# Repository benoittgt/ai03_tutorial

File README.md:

# ai03_tutorial

⚠️ This is a prototype that has not been builded for the moment. I am waiting for review ⚠️

Thanks ai03 and Ruiqi Mao for this very good guide (baby steps, shortcuts, many screenshots, electronic tips...).

## Feedbacks for [the original guide](https://kbwiki.ai03.me/books/pcb-design)

### [Part 4](https://kbwiki.ai03.me/books/pcb-design/page/pcb-guide-part-4---the-rest-of-the-schematic)
* Hard to find all schema. I had to import one by one lib from https://github.com/ldoiron17/Kicad_Libraries
* Different menu: "Switch to inch instead of mm on the left pane, and open Setup -> Design Rules." is Board Setup -> Design Rules -> Net classes
* Different menu: "Then click on the first corner of the zone to surround to bring up a menu." the "Copper Zone Properties" is different
### [Part 6](https://kbwiki.ai03.me/books/pcb-design/page/pcb-guide-part-6---fill-zones-decoration-and-production)
* Copper Zone Properties doesn't offer "Boundary mode" anymore
* When I try to simulate the board it's not delimited by the line 
* When I run the DRC the Molex connector have unclosed path so I need to switch
* DRC told be that "Driled holes too close together" for MX-1U

## Result

### PCB from Kicad

### Schema from Kicad

### Gerber file front and back rendered on JLPCB

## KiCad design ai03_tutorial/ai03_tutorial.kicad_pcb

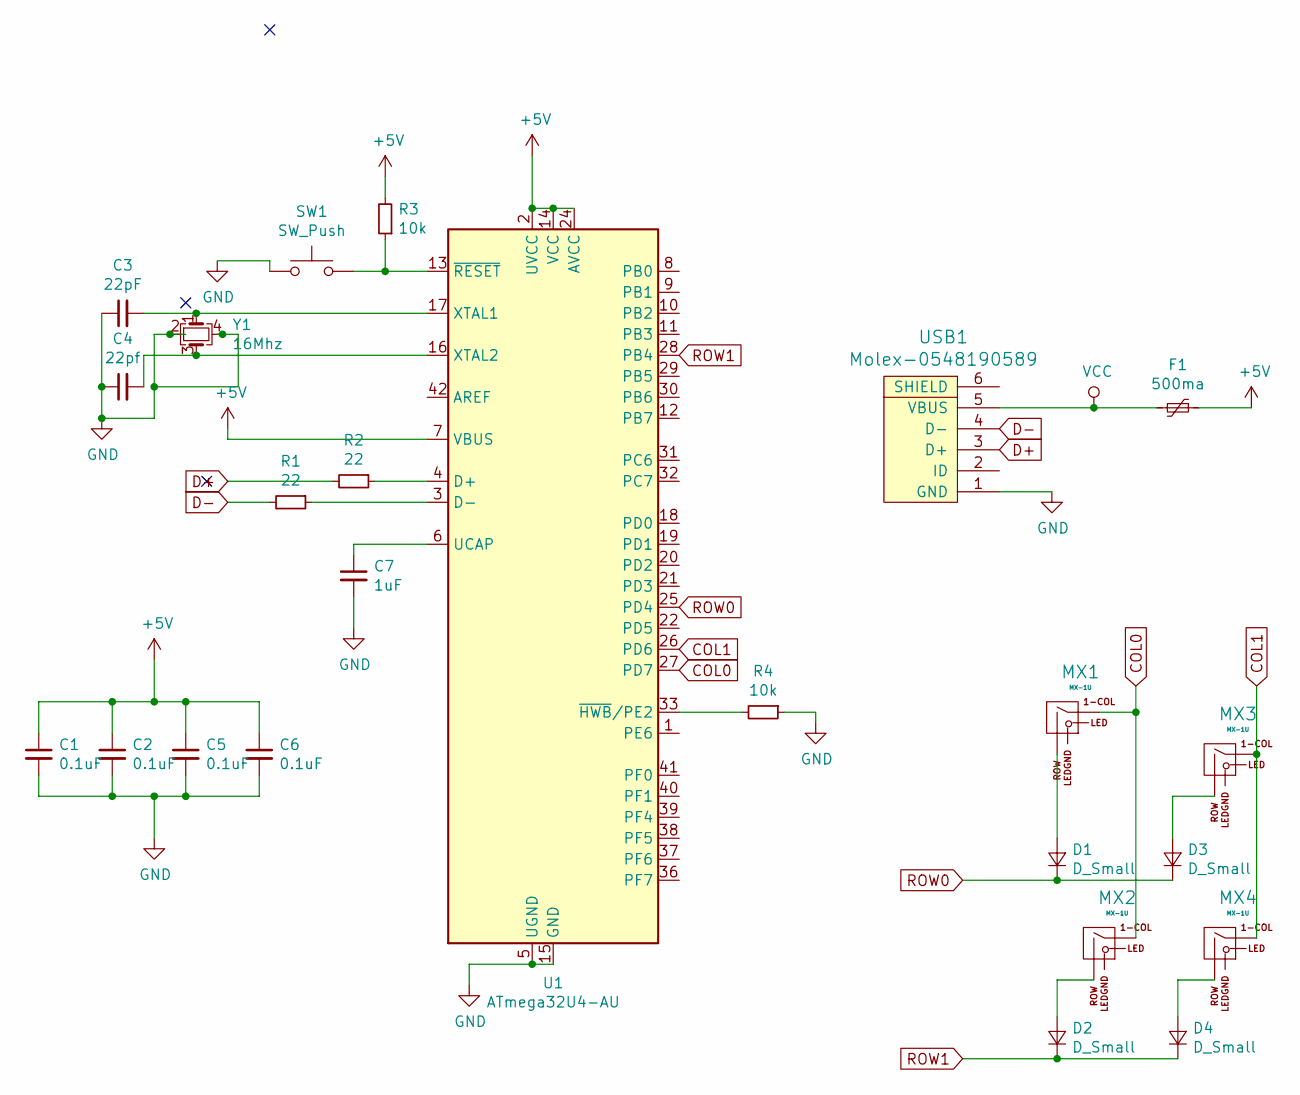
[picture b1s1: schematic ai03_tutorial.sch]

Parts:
C1, C2, C5, C6: 0.1uF; C_0805
C3: 22pF; C_0805
C4: 22pf; C_0805
C7: 1uF; C_0805
D1, D2, D3, D4: D_Small; D_SOD-123
F1: 500ma; Fuse_SMD1206_Reflow
MX1, MX2, MX3, MX4: MX-1U
R1, R2: 22; R_0805
R3, R4: 10k; R_0805
SW1: SW_Push; SKQG-1155865
U1: ATmega32U4-AU; TQFP-44_10x10mm_Pitch0.8mm
USB1: Molex-0548190589; USB_Micro-B_Molex-105017-0001
Y1: 16Mhz; Crystal_SMD_3225-4Pin_3.2x2.5mm

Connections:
+5V: C1.1, C2.1, C5.1, C6.1, F1.1, R3.2, U1.2 (UVCC), U1.7 (VBUS), U1.14 (VCC), U1.24 (AVCC), U1.34 (VCC), U1.44 (AVCC)
COL0: MX1.1 (COL), MX2.1 (COL), U1.27 (PD7)
COL1: MX3.1 (COL), MX4.1 (COL), U1.26 (PD6)
D+: R2.2, USB1.3 (D+)
D-: R1.2, USB1.4 (D-)
GND: C1.2, C2.2, C3.1, C4.1, C5.2, C6.2, C7.2, R4.1, SW1.1, U1.5 (UGND), U1.15 (GND), U1.23 (GND), U1.35 (GND), U1.43 (GND), USB1.1 (GND), Y1.2, Y1.4
unnamed: C3.2, U1.17 (XTAL1), Y1.1
unnamed: C4.2, U1.16 (XTAL2), Y1.3
unnamed: C7.1, U1.6 (UCAP)
unnamed: D1.2 (A), MX1.2 (ROW)
unnamed: D2.2 (A), MX2.2 (ROW)
unnamed: D3.2 (A), MX3.2 (ROW)
unnamed: D4.2 (A), MX4.2 (ROW)
unnamed: R1.1, U1.3 (D-)
unnamed: R2.1, U1.4 (D+)
unnamed: R3.1, SW1.2, U1.13 (~RESET)
unnamed: R4.2, U1.33 (~HWB~/PE2)
ROW0: D1.1 (K), D3.1 (K), U1.25 (PD4)
ROW1: D2.1 (K), D4.1 (K), U1.28 (PB4)
VCC: F1.2, USB1.5 (VBUS)

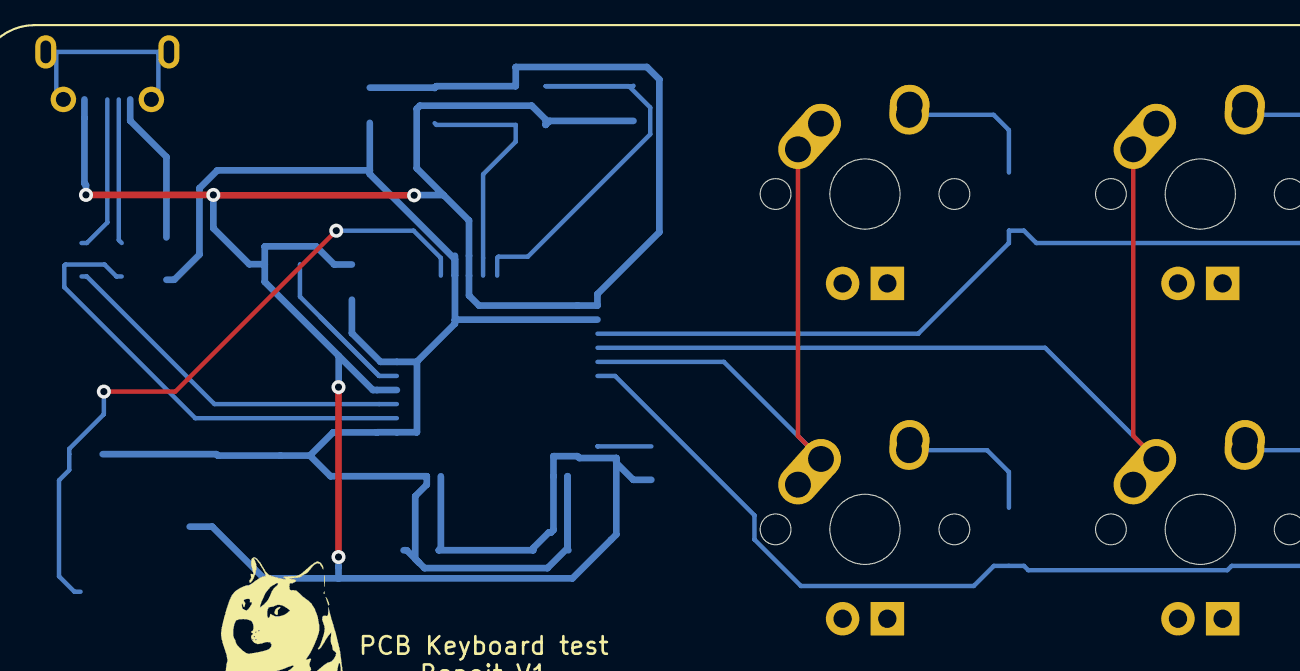
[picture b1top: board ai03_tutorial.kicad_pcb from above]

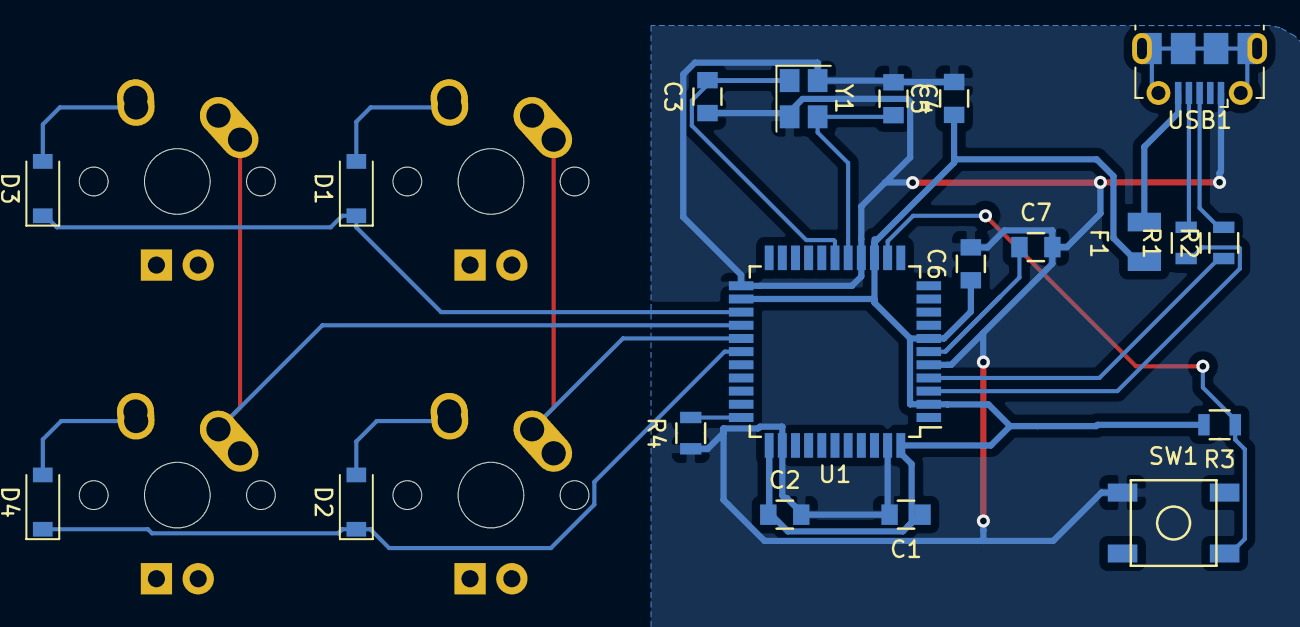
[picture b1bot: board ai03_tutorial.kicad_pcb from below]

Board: 2 copper layers, 24 parts (20 on the bottom side), 20 nets.

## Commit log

2019-01-27 Add lib for kicab with cherry profil
2019-01-27 Add schematic symbol and finish schema
2019-01-27 Add lib to kicad project
2019-01-27 New files
2019-01-27 First version of PCB
2019-01-27 Add new usb connector and plug keycaps
2019-01-27 Add first version : waiting for review
2019-01-27 Rename kicad pcb screenshot
2019-01-27 Better title for Gerber screenshot rendered
